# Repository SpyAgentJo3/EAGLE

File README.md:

# EAGLE
This repository contains all information and project files having to do with EAGLE a system designed for recovery and aerodynamic control of suborbital student rockets. EAGLE contains of a self-developed PCB and the mechanical design for a 16cm diameter rocket 

## Repository Structure

The repository is organized into the following main directories:

```text
├── ARCHER
│   ├── CAD Design
│   ├── Documentation
│   │   ├── Circuit Drawing
│   │   ├── Mechanical Design
│   │   ├── PCB
│   │   └── Software
│   ├── PCB Design
│   │   ├── CanSat Shield - Landesysteme v1.0.0
│   │   ├── EAGLE Recovery v1.0.0
│   │   ├── Footprint Library
│   │   ├── KiCAD 3D Models
│   │   ├── PCB Concept v2.0.0
│   │   └── Symbol Library
│   ├── Pyrochannels
│   ├── Simulation
│   ├── Software
│   │   └── EAGLE v1.2.1
│   │       ├── src
│   │       └── test
│   └── Misc
```

The repository contains the following main areas:

- **CAD Design** – CAD models and mechanical design files
- **Documentation** – Technical documentation, circuit diagrams, PCB documentation, and software-related documentation
- **PCB Design** – PCB layouts, libraries, concepts, recovery versions, and related design files
- **Pyrochannels** – Design files and backups related to the pyrochannel system
- **Simulation** – Simulation models and related files
- **Software** – Source code and tests for the project software
- **Misc** – Additional files that do not belong to the other categories

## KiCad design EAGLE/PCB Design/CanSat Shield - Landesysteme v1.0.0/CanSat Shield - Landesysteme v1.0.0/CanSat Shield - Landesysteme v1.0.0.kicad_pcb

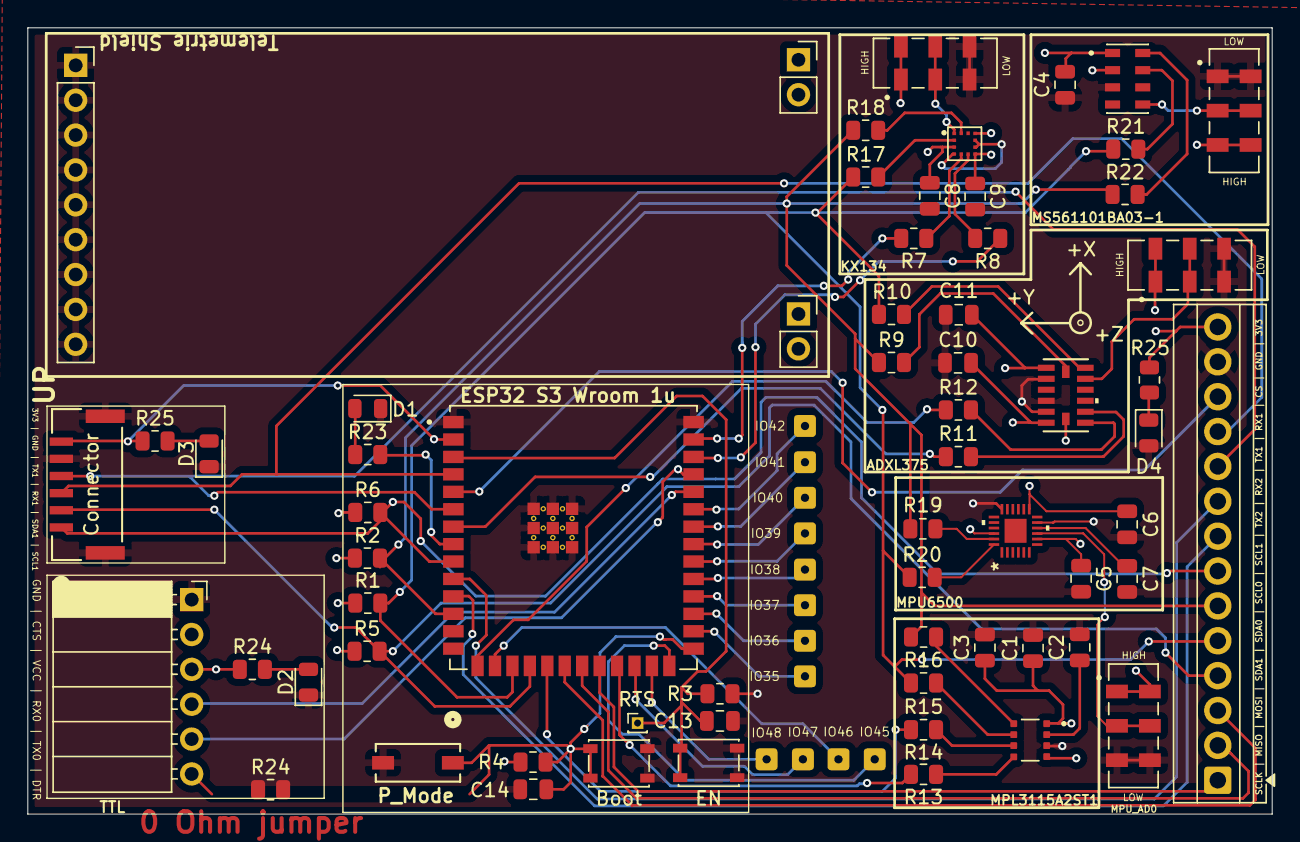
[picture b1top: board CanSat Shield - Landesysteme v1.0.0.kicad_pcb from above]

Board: 2 copper layers, 90.7 x 57.3 mm, 75 parts (0 on the bottom side), 56 nets.

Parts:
ADXL: JS202011JAQN (Switch); SW_JS202011JCQN
ADXL1: LGA_CC-14-1_ADI-M
Boot: SW_SPST_PTS810
C1, C2, C4, C13, C14: 100 nF; C_0805_2012Metric
C3: 10 uF; C_0805_2012Metric
C5: 10 nF; C_0805_2012Metric
C6: 0,1 uF; C_0805_2012Metric
C7, C8, C9, C11: 0.1 uF; C_0805_2012Metric
C10: 1 uF; C_0805_2012Metric
Connector: Connector; CONN_SM06B-GHS-TB_JST
D1, D2, D3, D4: 2V; LED_0805_2012Metric
EN: Works as reset button; SW_SPST_PTS810
ESP32 S3 Wroom 1u: ESP32-S3-WROOM-1U; XCVR_ESP32-S3-WROOM-1U
HIGH: JS202011JAQN (Switch); SW_JS202011JCQN
HIGH#2: JS202011JAQN (Switch); SW_JS202011JCQN
IO35, IO36, IO37, IO38, IO39, IO40, IO41, IO42, IO45, IO46, IO47, IO48: Conn_01x01; SolderWire-0.1sqmm_1x01_D0.4mm_OD1mm
J1: TTL; PinSocket_1x06_P2.54mm_Horizontal
J4: Tele-GND; PinSocket_1x09_P2.54mm_Vertical
J5, J6: Conn_01x02_Socket; PinSocket_1x02_P2.54mm_Vertical
KX1: XDCR_KX003-1077
MPL3115A2ST1: PSON80P300X300X100-8N
MPU6500: QFN24_3X3X0P9_IVS-M
MS561101BA03-1: XDCR_MS561101BA03-50
R1, R2, R3, R4, R5, R6: 10k; R_0805_2012Metric
R7, R8, R9, R10, R11, R12, R13, R14, R15, R16, R17, R18, R19, R20, R21, R22: 0R; R_0805_2012Metric
R23, R24, R24#2, R25, R25#2: 56R; R_0805_2012Metric
SCLK | MISO | MOSI | SDA1 | SDA0 | SCL0 | SCL1 | TX2 | RX2 | TX1 | RX1 | CS | GND | 3V3: Screw_Terminal_01x14; TerminalBlock_Xinya_XY308-2.54-14P_1x14_P2.54mm_Horizontal
SW1(Slideswitch)1: GND if disengaged, IO0 if engaged; SW_CHS-01TA_NDC
SW2: JS202011JAQN (Switch); SW_JS202011JCQN

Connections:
+3V3: ADXL.1, ADXL.5, ADXL1.CS, ADXL1.VDD, ADXL1.VDD_IO, C1.1, C3.1, C4.VDD, C5.VDD_IO, C6.VDD, C8.VDD_IO, C9.VDD, C10.VDD, C11.VDD_IO, Connector.6, ESP32 S3 Wroom 1u.VDD, HIGH.1, HIGH.5, HIGH#2.1, HIGH#2.5, J1.3, KX1.VDD, KX1.VDD_IO, KX1.nCS, MPL3115A2ST1.VDD, MPL3115A2ST1.VDD_IO, MPU6500.VDD, MPU6500.VDDIO, MPU6500.nCS, MS561101BA03-1.PS, MS561101BA03-1.VDD, R1.1, R2.1, R3.1, R4.1, R5.1, R6.1, R24#2.1, R25.2, R25#2.1, SCLK | MISO | MOSI | SDA1 | SDA0 | SCL0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.14, SW2.3, SW2.7
AD0: HIGH#2.2, HIGH#2.6, MPU6500.AD0
ADDR_ADXL: ADXL.2, ADXL.6, ADXL1.ADDR_ADXL
ADDR_KX: HIGH.2, HIGH.6, KX1.ADDR_KX
CS: ESP32 S3 Wroom 1u.5 (CS), SCLK | MISO | MOSI | SDA1 | SDA0 | SCL0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.12
GND1: ADXL.3, ADXL.7, ADXL1.2 (GND), ADXL1.4 (GND), ADXL1.5 (GND), Boot.1, Boot.2, C1.2, C2.2, C3.2, C4.2, C5.2, C6.1, C7.2, C8.2, C9.2, C10.2, C11.1, C13.2, C14.2, Connector.5, Connector.7, Connector.8, D1.1 (K), D2.1 (K), D3.1 (K), D4.2 (A), EN.1, EN.2, ESP32 S3 Wroom 1u.1 (GND), ESP32 S3 Wroom 1u.40 (GND), ESP32 S3 Wroom 1u.41_1 (GND), ESP32 S3 Wroom 1u.41_2 (GND), ESP32 S3 Wroom 1u.41_3 (GND), ESP32 S3 Wroom 1u.41_4 (GND), ESP32 S3 Wroom 1u.41_5 (GND), ESP32 S3 Wroom 1u.41_6 (GND), ESP32 S3 Wroom 1u.41_7 (GND), ESP32 S3 Wroom 1u.41_8 (GND), ESP32 S3 Wroom 1u.41_9 (GND), HIGH.3, HIGH.7, HIGH#2.3, HIGH#2.7, J1.1, J4.1, J4.2, J4.3, J4.4, J4.5, J4.6, J4.7, J4.8, J4.9, KX1.8 (GND), KX1.9 (GND), KX1.TRIG, MPL3115A2ST1.3, MPU6500.11 (FSYNC), MPU6500.18 (GND), MS561101BA03-1.3 (GND), SCLK | MISO | MOSI | SDA1 | SDA0 | SCL0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.13, SW1(Slideswitch)1.2, SW2.1, SW2.5
INT1_ADXL: ESP32 S3 Wroom 1u.15 (IO3), R12.2
INT1_KX: ESP32 S3 Wroom 1u.39 (IO1), R7.2
INT1_MPL: ESP32 S3 Wroom 1u.19 (IO11), R14.2
INT2_ADXL: ESP32 S3 Wroom 1u.7 (IO7), R11.1
INT2_KX: ESP32 S3 Wroom 1u.38 (IO2), R8.2
INT2_MPL: ESP32 S3 Wroom 1u.23 (IO21), R13.2
IO0: Boot.1, Boot.2, C14.1, ESP32 S3 Wroom 1u.27 (IO0_(Programming)), J1.6, R4.2, SW1(Slideswitch)1.1
MISO: ESP32 S3 Wroom 1u.21 (MISO), SCLK | MISO | MOSI | SDA1 | SDA0 | SCL0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.2
MOSI: ESP32 S3 Wroom 1u.20 (MOSI), SCLK | MISO | MOSI | SDA1 | SDA0 | SCL0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.3
unnamed: ADXL1.8 (INT1), R12.1
unnamed: ADXL1.9 (INT2), R11.2
unnamed: ADXL1.14 (SCL/SCLK), R9.2
unnamed: ADXL1.13 (SDA/SDI/SDIO), R10.2
unnamed: D1.2 (A), R23.1
unnamed: D2.2 (A), R24#2.2
unnamed: C13.1, EN.1, EN.2, ESP32 S3 Wroom 1u.3 (EN), R3.2
unnamed: ESP32 S3 Wroom 1u.LED (IO15), R23.2
unnamed: ESP32 S3 Wroom 1u.28 (IO35), IO35.1
unnamed: ESP32 S3 Wroom 1u.29 (IO36), IO36.1
unnamed: ESP32 S3 Wroom 1u.30 (IO37), IO37.1
unnamed: ESP32 S3 Wroom 1u.31 (IO38), IO38.1
unnamed: ESP32 S3 Wroom 1u.32 (IO39), IO39.1
unnamed: ESP32 S3 Wroom 1u.33 (IO40), IO40.1
unnamed: ESP32 S3 Wroom 1u.34 (IO41), IO41.1
unnamed: ESP32 S3 Wroom 1u.35 (IO42), IO42.1
unnamed: ESP32 S3 Wroom 1u.26 (IO45), IO45.1
unnamed: ESP32 S3 Wroom 1u.16 (IO46), IO46.1
unnamed: ESP32 S3 Wroom 1u.24 (IO47), IO47.1
unnamed: ESP32 S3 Wroom 1u.25 (IO48), IO48.1
unnamed: KX1.5 (INT1), R7.1
unnamed: KX1.6 (INT2), R8.1
unnamed: KX1.12 (SCLK/SCL), R18.2
unnamed: KX1.2 (SDI/SDA), R17.2
unnamed: C7.1, MPU6500.10 (REGOUT)
unnamed: MPU6500.23 (SCL/SCLK), R19.1
unnamed: MPU6500.24 (SDA/SDI), R20.2
unnamed: MS561101BA03-1.8 (SCLK), R22.1
unnamed: MS561101BA03-1.7 (SDI/SDA), R21.2
unnamed: MS561101BA03-1.4 (~CSB), MS561101BA03-1.CBS, SW2.2, SW2.6
RX0: ESP32 S3 Wroom 1u.36 (RXD0), J1.4
RX1: Connector.3, ESP32 S3 Wroom 1u.4 (RX1), SCLK | MISO | MOSI | SDA1 | SDA0 | SCL0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.11
RX2: ESP32 S3 Wroom 1u.10 (RX2), SCLK | MISO | MOSI | SDA1 | SDA0 | SCL0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.9
SCL0: ESP32 S3 Wroom 1u.12 (SCL0), R2.2, R9.1, R16.1, R18.1, R19.2, R22.2, SCLK | MISO | MOSI | SDA1 | SDA0 | SCL0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.6
SCL1: Connector.1, ESP32 S3 Wroom 1u.9 (SCL1), R6.2, SCLK | MISO | MOSI | SDA1 | SDA0 | SCL0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.7
SCLK: ESP32 S3 Wroom 1u.22 (SCLK), SCLK | MISO | MOSI | SDA1 | SDA0 | SCL0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.1
SDA0: ESP32 S3 Wroom 1u.17 (SDA0), R1.2, R10.1, R15.1, R17.1, R20.1, R21.1, SCLK | MISO | MOSI | SDA1 | SDA0 | SCL0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.5
SDA1: Connector.2, ESP32 S3 Wroom 1u.18 (SDA1), R5.2, SCLK | MISO | MOSI | SDA1 | SDA0 | SCL0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.4
TX0: ESP32 S3 Wroom 1u.37 (TXD0), J1.5
TX1: Connector.4, ESP32 S3 Wroom 1u.6 (TX1), SCLK | MISO | MOSI | SDA1 | SDA0 | SCL0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.10
TX2: ESP32 S3 Wroom 1u.11 (TX2), SCLK | MISO | MOSI | SDA1 | SDA0 | SCL0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.8

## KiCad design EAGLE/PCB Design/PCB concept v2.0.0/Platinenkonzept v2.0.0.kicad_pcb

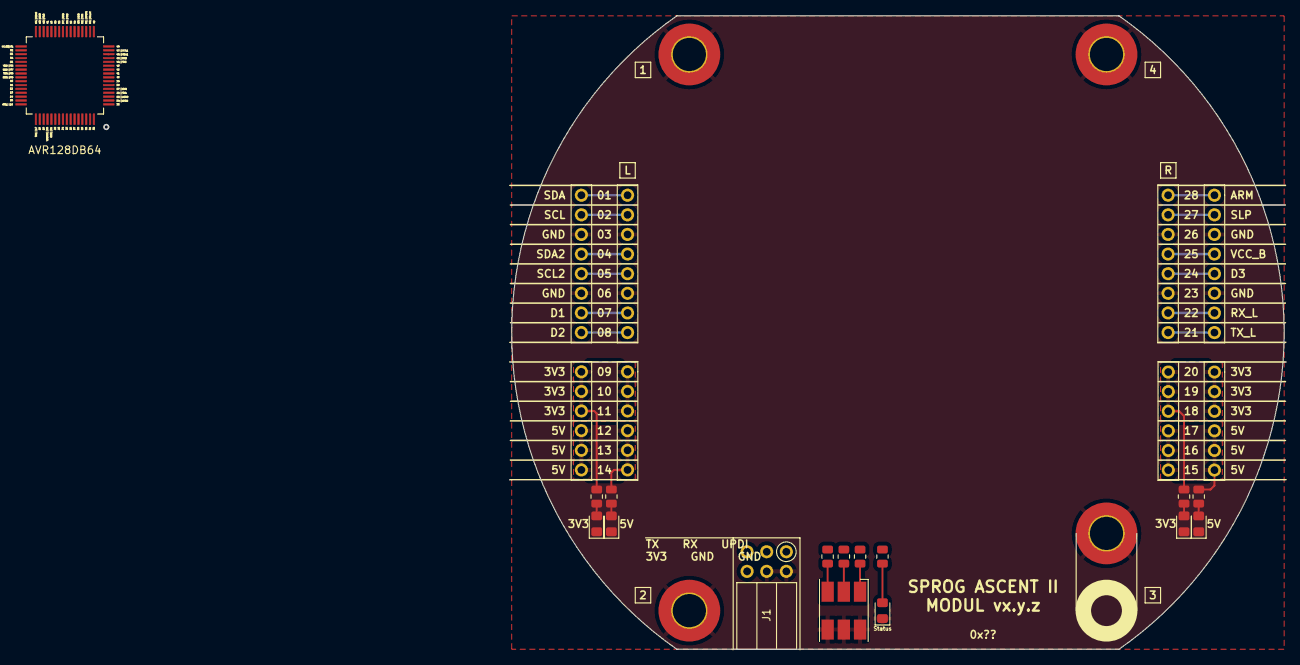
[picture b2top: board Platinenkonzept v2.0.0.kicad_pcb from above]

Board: 2 copper layers, 100.0 x 82.0 mm, 27 parts (0 on the bottom side), 19 nets.

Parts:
D1, D1#2, D1#3, D1#4, D1#5: LED; LED_0805_2012Metric_Pad1.15x1.40mm_HandSolder
D2: CLS6B-FKW; LED_RGB_Cree-PLCC-6_6x5mm_P2.1mm
J1: Conn_02x03_Odd_Even; PinSocket_2x03_P2.54mm_Horizontal
JL1, JL3: Conn_01x08_Pin; PinSocket_1x08_P2.54mm_Vertical
JL2, JL4: Conn_01x06_Pin; PinSocket_1x06_P2.54mm_Vertical
JR1, JR3: Conn_01x08_Pin; PinSocket_1x08_P2.54mm_Vertical
JR2, JR4: Conn_01x06_Pin; PinSocket_1x06_P2.54mm_Vertical
M1, M2, M3, M4: Conn_01x01_Pin; m4hole
R1, R1#2, R1#3, R1#4, R1#5, R2, R3, R4: R; R_0805_2012Metric

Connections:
+3V3: J1.2, JL2.9 (Pin_1), JL2.10 (Pin_2), JL2.11 (Pin_3), JL4.9 (Pin_1), JL4.10 (Pin_2), JL4.11 (Pin_3), JR2.18 (Pin_3), JR2.19 (Pin_2), JR2.20 (Pin_1), JR4.18 (Pin_3), JR4.19 (Pin_2), JR4.20 (Pin_1), R1#4.1, R1#5.1
+5V: JL2.12 (Pin_4), JL2.13 (Pin_5), JL2.14 (Pin_6), JL4.12 (Pin_4), JL4.13 (Pin_5), JL4.14 (Pin_6), JR2.15 (Pin_6), JR2.16 (Pin_5), JR2.17 (Pin_4), JR4.15 (Pin_6), JR4.16 (Pin_5), JR4.17 (Pin_4), R1#2.1, R1#3.1
ARM: JR1.28 (Pin_1), JR3.28 (Pin_1)
D1: JL1.7, JL3.7
D2: JL1.8, JL3.8
D3: JR1.24 (Pin_5), JR3.24 (Pin_5)
GND: D1.1 (K), D1#2.1 (K), D1#3.1 (K), D1#4.1 (K), D1#5.1 (K), D2.4 (KB), D2.5 (KR), D2.6 (KR), J1.4, J1.6, JL1.3, JL1.6, JL3.3, JL3.6, JR1.23 (Pin_6), JR1.26 (Pin_3), JR3.23 (Pin_6), JR3.26 (Pin_3), M1.1, M2.1, M3.1, M4.1
unnamed: D1.2 (A), D1#2.2 (A), D1#3.2 (A), D1#4.2 (A), D1#5.2 (A), R1.2, R1#2.2, R1#3.2, R1#4.2, R1#5.2
unnamed: D2.3 (AB), R4.2
unnamed: D2.2 (AG), R3.2
unnamed: D2.1 (AR), R2.2
RX_L: JR1.22 (Pin_7), JR3.22 (Pin_7)
SCL: JL1.2, JL3.2
SCL2: JL1.5, JL3.5
SDA: JL1.1, JL3.1
SDA2: JL1.4, JL3.4
SLP: JR1.27 (Pin_2), JR3.27 (Pin_2)
TX_L: JR1.21 (Pin_8), JR3.21 (Pin_8)
VCC_B: JR1.25 (Pin_4), JR3.25 (Pin_4)

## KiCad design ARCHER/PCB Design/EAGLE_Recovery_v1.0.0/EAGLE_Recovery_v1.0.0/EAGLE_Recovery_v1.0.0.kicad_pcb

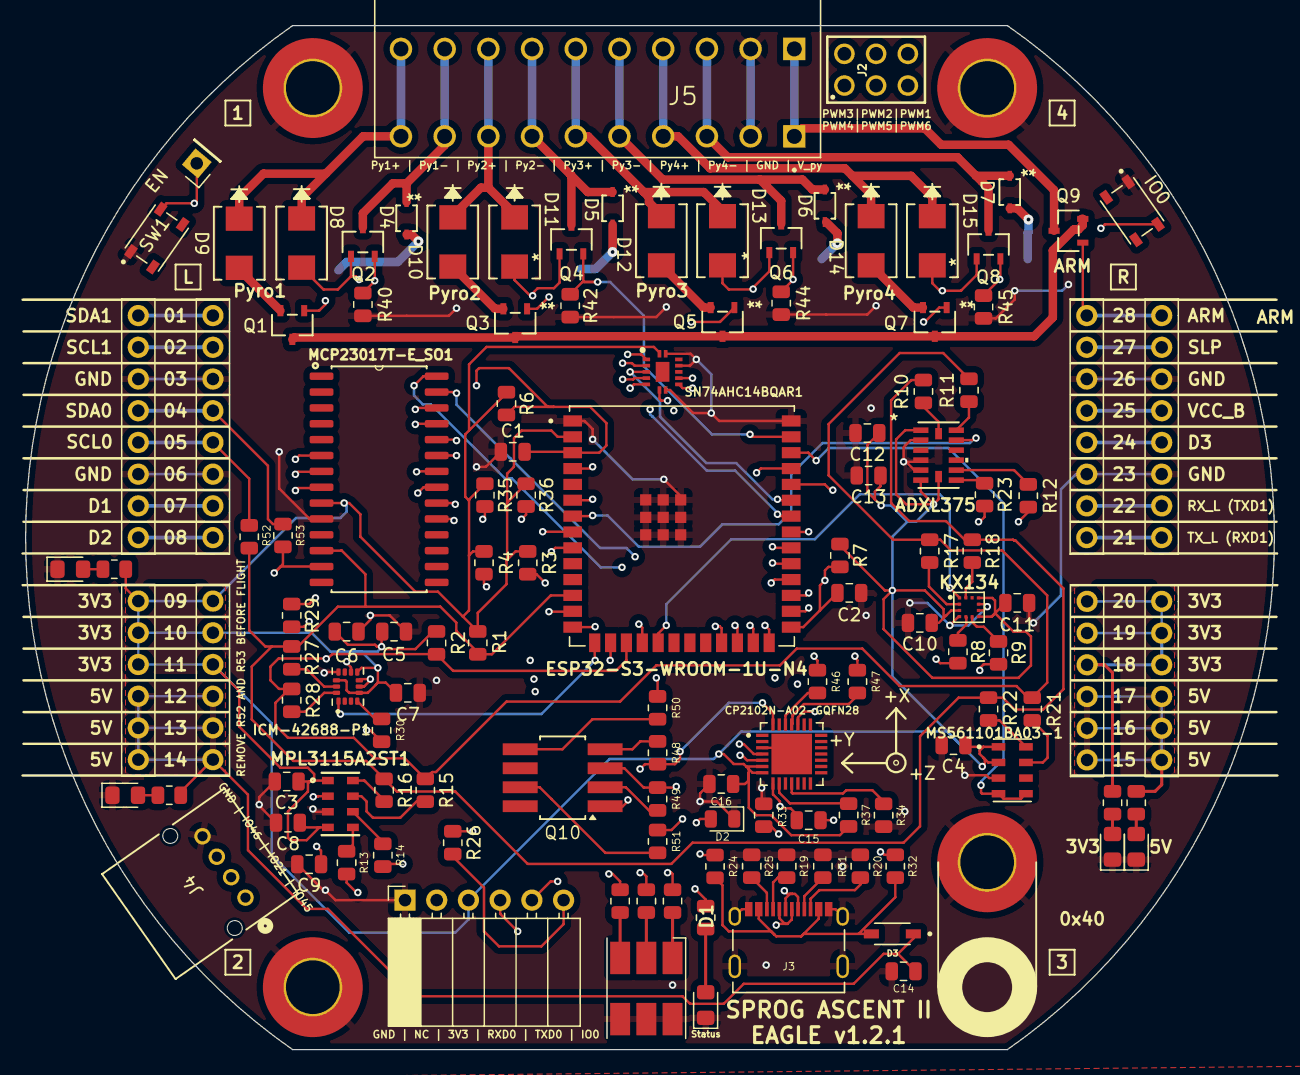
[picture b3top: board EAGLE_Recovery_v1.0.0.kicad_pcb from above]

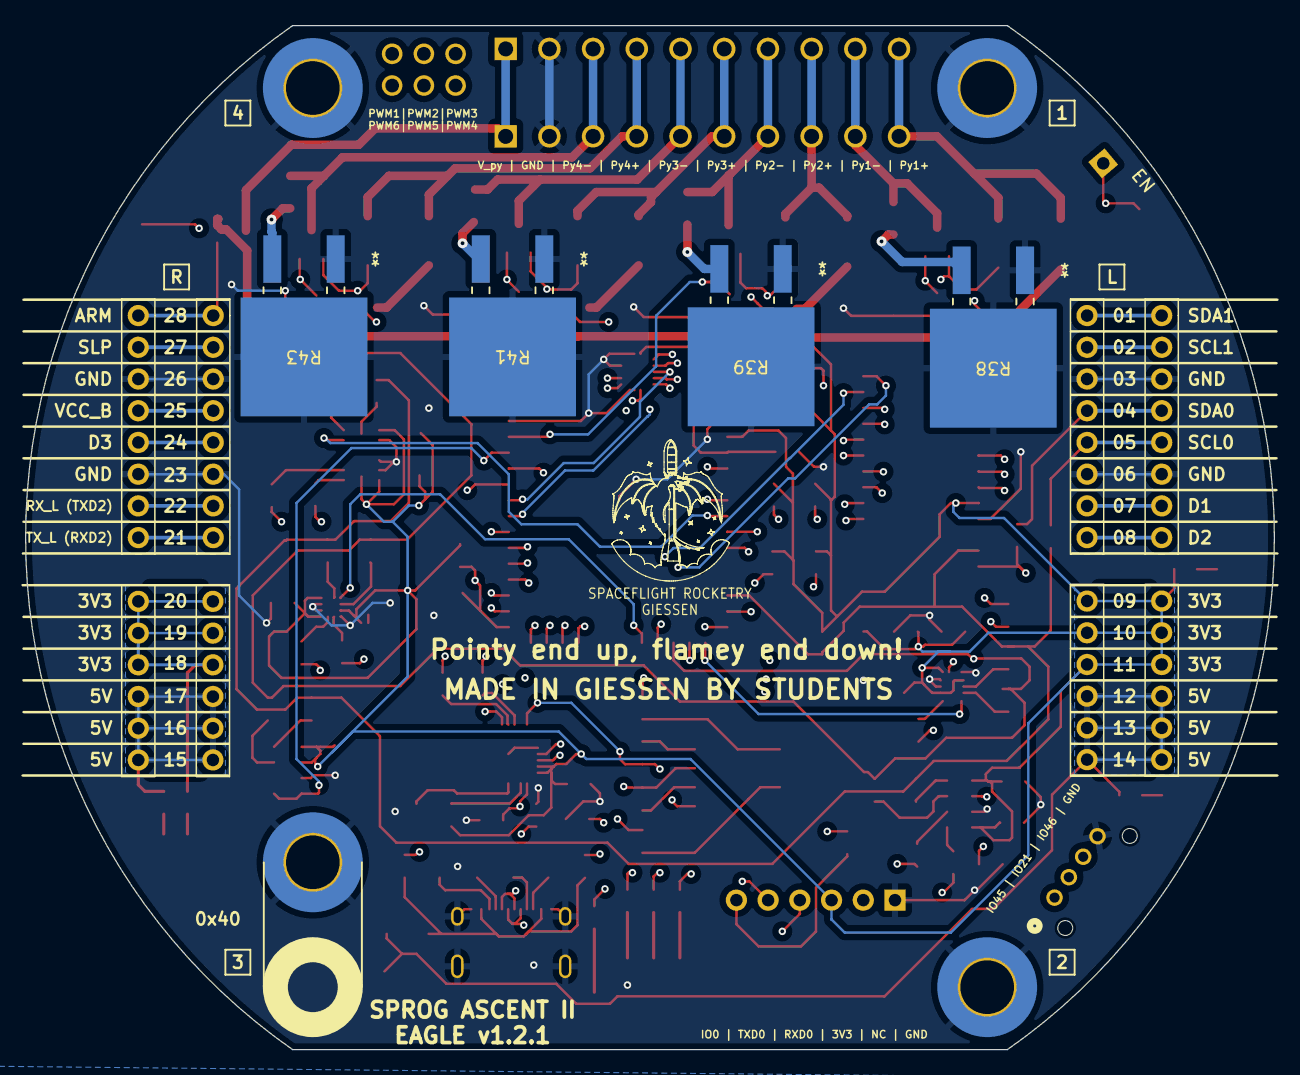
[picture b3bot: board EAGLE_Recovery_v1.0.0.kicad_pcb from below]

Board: 4 copper layers, 100.0 x 82.0 mm, 135 parts (4 on the bottom side), 115 nets.

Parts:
ADXL375: SPROG_ADXL375-M
C1, C2, C3, C4, C5, C7, C9: 100 nF; C_0805_2012Metric
C6: 2.2 uF; C_0805_2012Metric
C8, C14, C16: 10 uF; C_0805_2012Metric
C10, C11, C12: 0.1 uF; C_0805_2012Metric
C13, C15: 1 uF; C_0805_2012Metric
CP2102N-A02-GQFN28: CP2102N-A02-GQFN28; SPROG_CP2102N-A02-GQFN28
D1, D1#2, D1#3, D1#4, D1#5: LED; LED_0805_2012Metric_Pad1.15x1.40mm_HandSolder
D2: CLS6B-FKW; LED_RGB_Cree-PLCC-6_6x5mm_P2.1mm
D2#2: LED; LED_0805_2012Metric
D3: 1N5819HW-7-F; SPROG_1N5819HW-7-F
D4, D5, D6, D7: D_Zener_Small; SPROG_AQ4020_LTF
D8, D9, D10, D11, D12, D13, D14, D15: Shottkey; SPROG_DO214AA_MBRS_VIS
EN: RTS (EN); PinHeader_1x01_P2.54mm_Vertical
ESP32-S3-WROOM-1U-N4: ESP32-S3-WROOM-1U-N4; SPROG_ESP32-S3-WROOM-1U-N4
ICM-42688-P1: ICM-42688-P; SPROG_ICM-42688-P
IO0: Prog.; SPROG_SW_PTS810_SJM
J2: 6130XX21121_61300621121; SPROG_61300621121
J3: GSB1C411101DS1HR; SPROG_GSB1C411101DS1HR
J4: Screw_Terminal_01x04; SPROG_CONN4_S04B-PASK_JST
J5: TBLH10-350-10BK; SPROG_TBLH10-350-10BK
J6: TTL; PinSocket_1x06_P2.54mm_Horizontal
JL1, JL3: Conn_01x08_Pin; PinSocket_1x08_P2.54mm_Vertical
JL2, JL4: Conn_01x06_Pin; PinSocket_1x06_P2.54mm_Vertical
JR1, JR3: Conn_01x08_Pin; PinSocket_1x08_P2.54mm_Vertical
JR2, JR4: Conn_01x06_Pin; PinSocket_1x06_P2.54mm_Vertical
KX134: SPROG_KX134-1211
M1, M2, M3, M4: Conn_01x01_Pin; m4hole
MCP23017T-E_SO1: MCP23017T-E_SO; SPROG_MCP23017T-E_SO
MPL3115A2ST1: SPROG_MPL3115A2
MS561101BA03-1: SPROG_MS561101BA03-50
Q1, Q2, Q3, Q4, Q5, Q6, Q7, Q8, Q9: PMV37ENEAR; SPROG_SOT23_PMV37_NEX
Q10: NPN; Zetex_SM8
R1, R1#2, R1#3, R1#5, R1#6, R2#2, R3, R4#2: R; R_0805_2012Metric
R1#4, R2, R3#2, R4, R6, R7, R34, R35, R36, R48, R49: 10k; R_0805_2012Metric
R8, R9, R10, R11, R12, R13, R14, R15, R16, R17, R18, R21, R22, R23, R27, R28, R29, R30, R46, R47, R50, R51, R52, R53: 0R; R_0805_2012Metric
R19, R20, R31: 5R1; R_0805_2012Metric
R24: 56R; R_0805_2012Metric
R25: 50R; R_0805_2012Metric
R26: OR; R_0805_2012Metric
R32: 22k1; R_0805_2012Metric
R33: 47k5; R_0805_2012Metric
R37: 1k; R_0805_2012Metric
R38, R39, R43: 1R5; SPROG_RES_PWR263S-20-1R50J
R40, R42, R44, R45: 300k; R_0805_2012Metric
R41: 5R1; SPROG_RES_PWR263S-20-1R50J
SN74AHC14BQAR1: SN74AHC14BQAR; SPROG_SN74AHC14BQAR
SW1: EN; SPROG_SW_PTS810_SJM

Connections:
+3V3: ADXL375.1 (IO_VDD), ADXL375.6 (VDD), ADXL375.7 (CS), C3.1, C4.1, C5.1, C6.1, C7.1, C8.1, C10.1, C11.1, C12.2, C13.1, C16.1, CP2102N-A02-GQFN28.6 (VDD), CP2102N-A02-GQFN28.7 (VREGIN), ESP32-S3-WROOM-1U-N4.2 (3V3), ICM-42688-P1.5 (VDDIO), ICM-42688-P1.8 (VDD), ICM-42688-P1.12 (AP_CS), J6.3 (3V3), JL2.9 (Pin_1), JL2.10 (Pin_2), JL2.11 (Pin_3), JL4.9 (Pin_1), JL4.10 (Pin_2), JL4.11 (Pin_3), JR2.18 (Pin_3), JR2.19 (Pin_2), JR2.20 (Pin_1), JR4.18 (Pin_3), JR4.19 (Pin_2), JR4.20 (Pin_1), KX134.3 (IO_VDD), KX134.7 (VDD), KX134.10 (nCS), MCP23017T-E_SO1.9 (VDD), MPL3115A2ST1.1 (V_DD), MPL3115A2ST1.4 (V_DDIO), MS561101BA03-1.1 (VDD), MS561101BA03-1.2 (PS), R1#2.1, R1#4.1, R1#6.1, R2.1, R3#2.1, R4.1, R6.1, R7.1, R35.1, R36.1, R37.1, SN74AHC14BQAR1.14 (VCC)
+5V: C14.1, D3.C, JL2.12 (Pin_4), JL2.13 (Pin_5), JL2.14 (Pin_6), JL4.12 (Pin_4), JL4.13 (Pin_5), JL4.14 (Pin_6), JR2.15 (Pin_6), JR2.16 (Pin_5), JR2.17 (Pin_4), JR4.15 (Pin_6), JR4.16 (Pin_5), JR4.17 (Pin_4), R1.1, R1#5.1
ADDR_ADXL: ADXL375.12 (SDO/ADDR), ESP32-S3-WROOM-1U-N4.7 (IO7)
ADDR_KX: ESP32-S3-WROOM-1U-N4.19 (IO11), KX134.1 (SDO/ADDR)
ADO_ICM: ESP32-S3-WROOM-1U-N4.15 (IO3), ICM-42688-P1.1 (AP_SDO/AP_AD0)
ARM: JR1.28 (Pin_1), JR3.28 (Pin_1), Q9.1 (G)
CSB: ESP32-S3-WROOM-1U-N4.38 (IO2), MS561101BA03-1.4 (~CSB), MS561101BA03-1.5 (~CSB)
D1: JL1.7, JL3.7
D2: JL1.8, JL3.8
D3: JR1.24 (Pin_5), JR3.24 (Pin_5)
D+: CP2102N-A02-GQFN28.4 (D+), ESP32-S3-WROOM-1U-N4.14 (IO20/USB_D+), J3.A6 (D1+), J3.B6 (D2+)
D-: CP2102N-A02-GQFN28.5 (D-), ESP32-S3-WROOM-1U-N4.13 (IO19/USB_D-), J3.A7 (D1-), J3.B7 (D2-)
DTR: CP2102N-A02-GQFN28.28 (DTR), Q10.1 (C), R48.2
EN: C1.2, EN.1, ESP32-S3-WROOM-1U-N4.3 (EN), R6.2, R50.2, SW1.2
GND: ADXL375.2 (GND), ADXL375.4 (GND), ADXL375.5 (GND), C1.1, C2.2, C3.2, C4.2, C5.2, C6.2, C7.2, C8.2, C9.2, C10.2, C11.2, C12.1, C13.2, C14.2, C15.2, C16.2, CP2102N-A02-GQFN28.3 (GND), CP2102N-A02-GQFN28.29 (GND__1), D1.1 (K), D1#2.1 (K), D1#3.1 (K), D1#4.1 (K), D1#5.1 (K), D2.4 (KB), D2.5 (KR), D2.6 (KR), D2#2.1 (K), ESP32-S3-WROOM-1U-N4.1 (GND), ESP32-S3-WROOM-1U-N4.40 (GND), ESP32-S3-WROOM-1U-N4.41_1 (GND), ESP32-S3-WROOM-1U-N4.41_2 (GND), ESP32-S3-WROOM-1U-N4.41_3 (GND), ESP32-S3-WROOM-1U-N4.41_4 (GND), ESP32-S3-WROOM-1U-N4.41_5 (GND), ESP32-S3-WROOM-1U-N4.41_6 (GND), ESP32-S3-WROOM-1U-N4.41_7 (GND), ESP32-S3-WROOM-1U-N4.41_8 (GND), ESP32-S3-WROOM-1U-N4.41_9 (GND), ICM-42688-P1.6 (GND), ICM-42688-P1.7 (RESV_7), ICM-42688-P1.11 (RESV_11), IO0.1 (A), J3.A1B12 (GND_A), J3.B1A12 (GND_B), J3.SH1 (SHIELD), J3.SH2 (SHIELD__1), J3.SH3 (SHIELD__2), J3.SH4 (SHIELD__3), J4.4, J5.2_A (2), J5.2_B (2__1), J6.1 (GND), JL1.3, JL1.6, JL3.3, JL3.6, JR1.23 (Pin_6), JR1.26 (Pin_3), JR3.23 (Pin_6), JR3.26 (Pin_3), KX134.4 (TRIG), KX134.8 (GND), KX134.9 (GND), M1.1, M2.1, M3.1, M4.1, MCP23017T-E_SO1.10 (VSS), MPL3115A2ST1.3 (GND), MS561101BA03-1.3 (GND), R19.2, R20.1, R25.1, R31.1, R33.2, R34.1, R38.1, R38.2, R39.1, R39.2, R40.2, R41.1, R41.2, R42.2, R43.1, R43.2, R44.2, R45.2, SN74AHC14BQAR1.7 (GND), SN74AHC14BQAR1.11 (5A), SN74AHC14BQAR1.13 (6A), SW1.1
INT1_ADXL: MCP23017T-E_SO1.24 (GPA3), R23.2
INT1_ICM: MCP23017T-E_SO1.25 (GPA4), R30.2
INT1_KX: MCP23017T-E_SO1.27 (GPA6), R8.2
INT1_MPL: MCP23017T-E_SO1.21 (GPA0), R14.2
INT2_ADXL: MCP23017T-E_SO1.23 (GPA2), R12.1
INT2_ICM: MCP23017T-E_SO1.26 (GPA5), R29.1
INT2_KX: MCP23017T-E_SO1.28 (GPA7), R9.2
INT2_MPL: MCP23017T-E_SO1.22 (GPA1), R13.2
IO0: C2.1, ESP32-S3-WROOM-1U-N4.27 (IO0_(P)), IO0.2 (B), R7.2, R26.2, R51.2
IO1/Cont.: ESP32-S3-WROOM-1U-N4.39 (IO1/Cont.), Q2.2 (S), Q4.2 (S), Q6.2 (S), Q8.2 (S), R40.1, R42.1, R44.1, R45.1
IO21: ESP32-S3-WROOM-1U-N4.23 (IO21), J4.2
IO41: ESP32-S3-WROOM-1U-N4.34 (IO41/Pyro1), Q1.1 (G), SN74AHC14BQAR1.1 (1A)
IO42: ESP32-S3-WROOM-1U-N4.35 (IO42/Pyro2), Q3.1 (G), SN74AHC14BQAR1.3 (2A)
IO45: ESP32-S3-WROOM-1U-N4.26 (IO45), J4.1
IO46/Conf.: ESP32-S3-WROOM-1U-N4.16 (IO46/Conf.), J4.3
IO47: ESP32-S3-WROOM-1U-N4.24 (IO47/Pyro3), Q5.1 (G), SN74AHC14BQAR1.5 (3A)
IO48: ESP32-S3-WROOM-1U-N4.25 (IO48/Pyro4), Q7.1 (G), SN74AHC14BQAR1.9 (4A)
LED B: MCP23017T-E_SO1.8 (GPB7), R4#2.1
LED G: MCP23017T-E_SO1.7 (GPB6), R3.1
LED R: MCP23017T-E_SO1.6 (GPB5), R2#2.1
unnamed: ADXL375.8 (INT1), R23.1
unnamed: ADXL375.9 (INT2), R12.2
unnamed: ADXL375.14 (SCL/SCLK), R10.2
unnamed: ADXL375.13 (SDA/SDI/SDIO), R11.2
unnamed: CP2102N-A02-GQFN28.25 (RXD), R47.1
unnamed: CP2102N-A02-GQFN28.26 (TXD), R46.1
unnamed: C15.1, CP2102N-A02-GQFN28.8 (VBUS), R32.1, R33.1
unnamed: CP2102N-A02-GQFN28.9 (~RST), R37.2
unnamed: CP2102N-A02-GQFN28.11 (~SUSPEND), R34.2
unnamed: D1.2 (A), D1#2.2 (A), D1#3.2 (A), D1#4.2 (A), D1#5.2 (A), R1.2, R1#2.2, R1#3.2, R1#5.2, R1#6.2
unnamed: D2#2.2 (A), R24.2
unnamed: D2.3 (AB), R4#2.2
unnamed: D2.2 (AG), R3.2
unnamed: D2.1 (AR), R2#2.2
unnamed: D4.2 (A), R38.3
unnamed: D5.2 (A), R39.3
unnamed: D6.2 (A), R41.3
unnamed: D7.2 (A), R43.3
unnamed: D9.2 (A), Q1.2 (S)
unnamed: D10.2 (A), Q3.2 (S)
unnamed: D12.2 (A), Q5.2 (S)
unnamed: D14.2 (A), Q7.2 (S)
unnamed: ESP32-S3-WROOM-1U-N4.8 (IO15/LED1), R1#3.1
unnamed: ESP32-S3-WROOM-1U-N4.28 (IO35/PWM1), J2.6
unnamed: ESP32-S3-WROOM-1U-N4.29 (IO36/PWM2), J2.4
unnamed: ESP32-S3-WROOM-1U-N4.30 (IO37/PWM3), J2.2
unnamed: ESP32-S3-WROOM-1U-N4.31 (IO38/PWM4), J2.1
unnamed: ESP32-S3-WROOM-1U-N4.32 (IO39/PWM5), J2.3
unnamed: ESP32-S3-WROOM-1U-N4.33 (IO40/PWM6), J2.5
unnamed: ICM-42688-P1.13 (AP_SCL/AP_SCLK), R27.2
unnamed: ICM-42688-P1.14 (AP_SDA/AP_SDIO/AP_SDI), R28.1
unnamed: ICM-42688-P1.4 (INT1/INT), R30.1
unnamed: ICM-42688-P1.9 (INT2/FSYNC/CLKIN), R29.2
unnamed: J3.A5 (CC1), R19.1
unnamed: J3.B5 (CC2), R20.2
unnamed: J3.A8 (SBU1), R31.2
unnamed: J3.B8 (SBU2), R25.2
unnamed: J6.6 (IO0), R26.1
unnamed: KX134.5 (INT1), R8.1
unnamed: KX134.6 (INT2), R9.1
unnamed: KX134.12 (SCLK/SCL), R18.2
unnamed: KX134.2 (SDI/SDA), R17.2
unnamed: MCP23017T-E_SO1.20 (INTA), R36.2
unnamed: MCP23017T-E_SO1.19 (INTB), R35.2
unnamed: C9.1, MPL3115A2ST1.2 (CAP)
unnamed: MPL3115A2ST1.6 (INT1), R14.1
unnamed: MPL3115A2ST1.5 (INT2), R13.1
unnamed: MPL3115A2ST1.8 (SCL), R16.2
unnamed: MPL3115A2ST1.7 (SDL), R15.2
unnamed: MS561101BA03-1.8 (SCLK), R22.1
unnamed: MS561101BA03-1.7 (SDI/SDA), R21.2
unnamed: Q10.4, R48.1
unnamed: Q10.5, Q10.6, R50.1
unnamed: Q10.2 (B), R49.1
unnamed: Q10.7, Q10.8, R51.1
Py1+: D8.1 (K), D9.1 (K), J5.10_A (10), J5.10_B (10__1)
Py1-: D4.1 (K), J5.9_A (9), J5.9_B (9__1), Q2.3 (D)
Py2+: D10.1 (K), D11.1 (K), J5.8_A (8), J5.8_B (8__1)
Py2-: D5.1 (K), J5.7_A (7), J5.7_B (7__1), Q4.3 (D)
Py3+: D12.1 (K), D13.1 (K), J5.6_A (6), J5.6_B (6__1)
Py3-: D6.1 (K), J5.5_A (5), J5.5_B (5__1), Q6.3 (D)
Py4+: D14.1 (K), D15.1 (K), J5.4_A (4), J5.4_B (4__1)
Py4-: D7.1 (K), J5.3_A (3), J5.3_B (3__1), Q8.3 (D)
Pyro1 (IO41): D8.2 (A), Q2.1 (G), SN74AHC14BQAR1.2 (1Y)
Pyro2 (IO42): D11.2 (A), Q4.1 (G), SN74AHC14BQAR1.4 (2Y)
Pyro3 (IO47): D13.2 (A), Q6.1 (G), SN74AHC14BQAR1.6 (3Y)
Pyro4 (IO48): D15.2 (A), Q8.1 (G), SN74AHC14BQAR1.8 (4Y)
RTS: CP2102N-A02-GQFN28.24 (RTS), Q10.3 (E), R49.2
RXD0: ESP32-S3-WROOM-1U-N4.36 (IO44/RXD0), J6.4 (RXD0), R47.2
RXD1: ESP32-S3-WROOM-1U-N4.4 (IO4/RXD1), JR1.21 (Pin_8), JR3.21 (Pin_8)
SCL0: ESP32-S3-WROOM-1U-N4.12 (IO8/SCL0), JL1.5, JL3.5, MCP23017T-E_SO1.12 (SCK), R1#4.2, R10.1, R16.1, R18.1, R22.2, R27.1, R52.1, R52.2
SCL1: ESP32-S3-WROOM-1U-N4.9 (IO16/SCL1), JL1.2, JL3.2, R4.2
SDA0: ESP32-S3-WROOM-1U-N4.17 (IO9/SDA0), JL1.4, JL3.4, MCP23017T-E_SO1.13 (SDA), R2.2, R11.1, R15.1, R17.1, R21.1, R28.2, R53.1, R53.2
SDA1: ESP32-S3-WROOM-1U-N4.18 (IO10/SDA1), JL1.1, JL3.1, R3#2.2
SLP: JR1.27 (Pin_2), JR3.27 (Pin_2)
TXD0: ESP32-S3-WROOM-1U-N4.37 (IO43/TXD0), J6.5 (TXD0), R46.2
TXD1: ESP32-S3-WROOM-1U-N4.6 (IO6/TXD1), JR1.22 (Pin_7), JR3.22 (Pin_7)
VBUS: D3.A, J3.A4B9 (VBUS_A), J3.B4A9 (VBUS_B), R24.1, R32.2
VCC_B: JR1.25 (Pin_4), JR3.25 (Pin_4)
V_py: J5.1_A (1), J5.1_B (1__1), Q1.3 (D), Q3.3 (D), Q5.3 (D), Q7.3 (D), Q9.2 (S), Q9.3 (D)
